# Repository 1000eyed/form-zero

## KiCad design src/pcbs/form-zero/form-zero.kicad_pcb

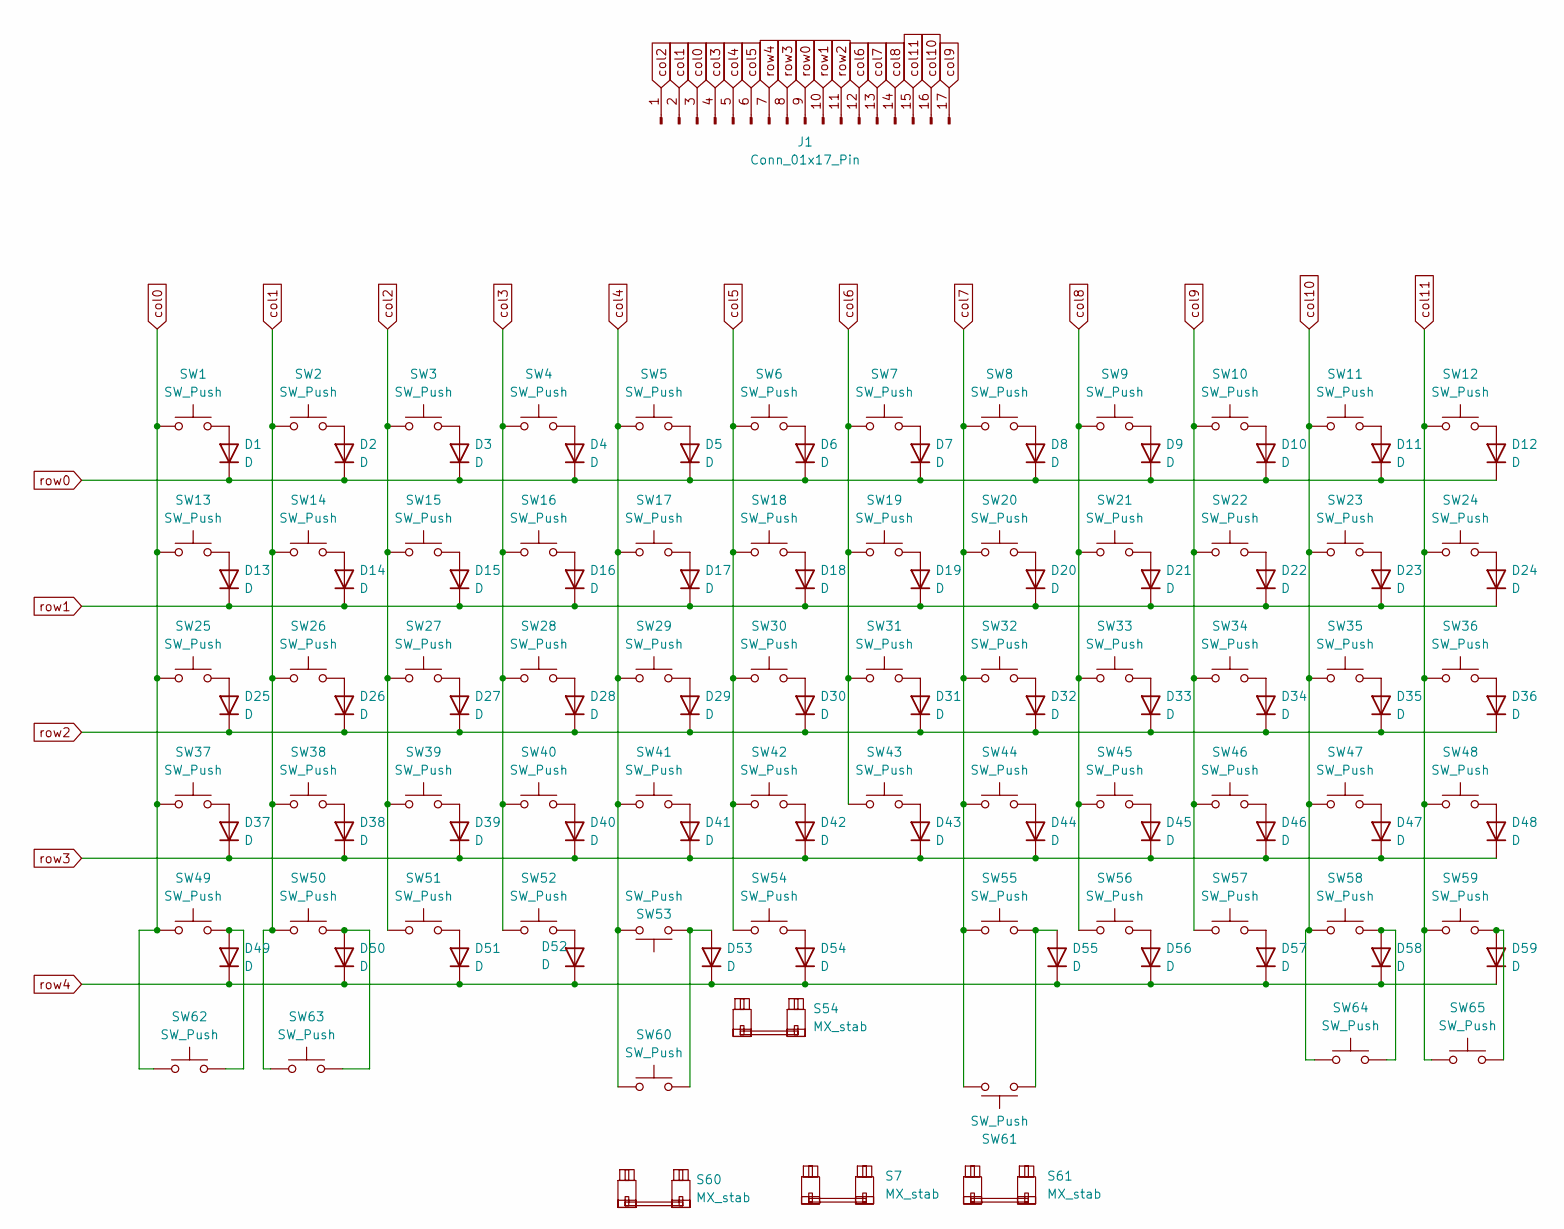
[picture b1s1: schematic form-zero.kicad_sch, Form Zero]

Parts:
D1, D2, D3, D4, D5, D6, D7, D8, D9, D10, D11, D12, D13, D14, D15, D16, D17, D18, D19, D20, D21, D22, D23, D24, D25, D26, D27, D28, D29, D30, D31, D32, D33, D34, D35, D36, D37, D38, D39, D40, D41, D42, D43, D44, D45, D46, D47, D48, D49, D50, D51, D52, D53, D54, D55, D56, D57, D58, D59: D; D3_TH_SMD_v2
J1: Conn_01x17_Pin; PinHeader_1x17_P2.54mm_Vertical
S7: MX_stab; STAB_MX_7u
S54, S60, S61: MX_stab; STAB_MX_2u
SW1, SW2, SW3, SW4, SW5, SW6, SW7, SW8, SW9, SW10, SW11, SW12, SW13, SW14, SW15, SW16, SW17, SW18, SW19, SW20, SW21, SW22, SW23, SW24, SW25, SW26, SW27, SW28, SW29, SW30, SW31, SW32, SW33, SW34, SW35, SW36, SW37, SW38, SW39, SW40, SW41, SW42, SW43, SW44, SW45, SW46, SW47, SW48, SW49, SW50, SW51, SW52, SW53, SW54, SW55, SW56, SW57, SW58, SW59, SW60, SW61: SW_Push; SW_MX_HS_CPG151101S11_1u
SW62, SW63, SW64, SW65: SW_Push; SW_MX_HS_CPG151101S11_1.25u

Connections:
unnamed: D1.2 (A), SW1.2
unnamed: D2.2 (A), SW2.2
unnamed: D3.2 (A), SW3.2
unnamed: D4.2 (A), SW4.2
unnamed: D5.2 (A), SW5.2
unnamed: D6.2 (A), SW6.2
unnamed: D7.2 (A), SW7.2
unnamed: D8.2 (A), SW8.2
unnamed: D9.2 (A), SW9.2
unnamed: D10.2 (A), SW10.2
unnamed: D11.2 (A), SW11.2
unnamed: D12.2 (A), SW12.2
unnamed: D13.2 (A), SW13.2
unnamed: D14.2 (A), SW14.2
unnamed: D15.2 (A), SW15.2
unnamed: D16.2 (A), SW16.2
unnamed: D17.2 (A), SW17.2
unnamed: D18.2 (A), SW18.2
unnamed: D19.2 (A), SW19.2
unnamed: D20.2 (A), SW20.2
unnamed: D21.2 (A), SW21.2
unnamed: D22.2 (A), SW22.2
unnamed: D23.2 (A), SW23.2
unnamed: D24.2 (A), SW24.2
unnamed: D25.2 (A), SW25.2
unnamed: D26.2 (A), SW26.2
unnamed: D27.2 (A), SW27.2
unnamed: D28.2 (A), SW28.2
unnamed: D29.2 (A), SW29.2
unnamed: D30.2 (A), SW30.2
unnamed: D31.2 (A), SW31.2
unnamed: D32.2 (A), SW32.2
unnamed: D33.2 (A), SW33.2
unnamed: D34.2 (A), SW34.2
unnamed: D35.2 (A), SW35.2
unnamed: D36.2 (A), SW36.2
unnamed: D37.2 (A), SW37.2
unnamed: D38.2 (A), SW38.2
unnamed: D39.2 (A), SW39.2
unnamed: D40.2 (A), SW40.2
unnamed: D41.2 (A), SW41.2
unnamed: D42.2 (A), SW42.2
unnamed: D43.2 (A), SW43.2
unnamed: D44.2 (A), SW44.2
unnamed: D45.2 (A), SW45.2
unnamed: D46.2 (A), SW46.2
unnamed: D47.2 (A), SW47.2
unnamed: D48.2 (A), SW48.2
unnamed: D49.2 (A), SW49.2, SW62.2
unnamed: D50.2 (A), SW50.2, SW63.2
unnamed: D51.2 (A), SW51.2
unnamed: D52.2 (A), SW52.2
unnamed: D53.2 (A), SW53.1, SW60.2
unnamed: D54.2 (A), SW54.2
unnamed: D55.2 (A), SW55.2, SW61.1
unnamed: D56.2 (A), SW56.2
unnamed: D57.2 (A), SW57.2
unnamed: D58.2 (A), SW58.2, SW64.2
unnamed: D59.2 (A), SW59.2, SW65.2
col0: J1.3, SW1.1, SW13.1, SW25.1, SW37.1, SW49.1, SW62.1
col1: J1.2, SW2.1, SW14.1, SW26.1, SW38.1, SW50.1, SW63.1
col2: J1.1, SW3.1, SW15.1, SW27.1, SW39.1, SW51.1
col3: J1.4, SW4.1, SW16.1, SW28.1, SW40.1, SW52.1
col4: J1.5, SW5.1, SW17.1, SW29.1, SW41.1, SW53.2, SW60.1
col5: J1.6, SW6.1, SW18.1, SW30.1, SW42.1, SW54.1
col6: J1.12, SW7.1, SW19.1, SW31.1, SW43.1
col7: J1.13, SW8.1, SW20.1, SW32.1, SW44.1, SW55.1, SW61.2
col8: J1.14, SW9.1, SW21.1, SW33.1, SW45.1, SW56.1
col9: J1.17, SW10.1, SW22.1, SW34.1, SW46.1, SW57.1
col10: J1.16, SW11.1, SW23.1, SW35.1, SW47.1, SW58.1, SW64.1
col11: J1.15, SW12.1, SW24.1, SW36.1, SW48.1, SW59.1, SW65.1
row0: D1.1 (K), D2.1 (K), D3.1 (K), D4.1 (K), D5.1 (K), D6.1 (K), D7.1 (K), D8.1 (K), D9.1 (K), D10.1 (K), D11.1 (K), D12.1 (K), J1.9
row1: D13.1 (K), D14.1 (K), D15.1 (K), D16.1 (K), D17.1 (K), D18.1 (K), D19.1 (K), D20.1 (K), D21.1 (K), D22.1 (K), D23.1 (K), D24.1 (K), J1.10
row2: D25.1 (K), D26.1 (K), D27.1 (K), D28.1 (K), D29.1 (K), D30.1 (K), D31.1 (K), D32.1 (K), D33.1 (K), D34.1 (K), D35.1 (K), D36.1 (K), J1.11
row3: D37.1 (K), D38.1 (K), D39.1 (K), D40.1 (K), D41.1 (K), D42.1 (K), D43.1 (K), D44.1 (K), D45.1 (K), D46.1 (K), D47.1 (K), D48.1 (K), J1.8
row4: D49.1 (K), D50.1 (K), D51.1 (K), D52.1 (K), D53.1 (K), D54.1 (K), D55.1 (K), D56.1 (K), D57.1 (K), D58.1 (K), D59.1 (K), J1.7

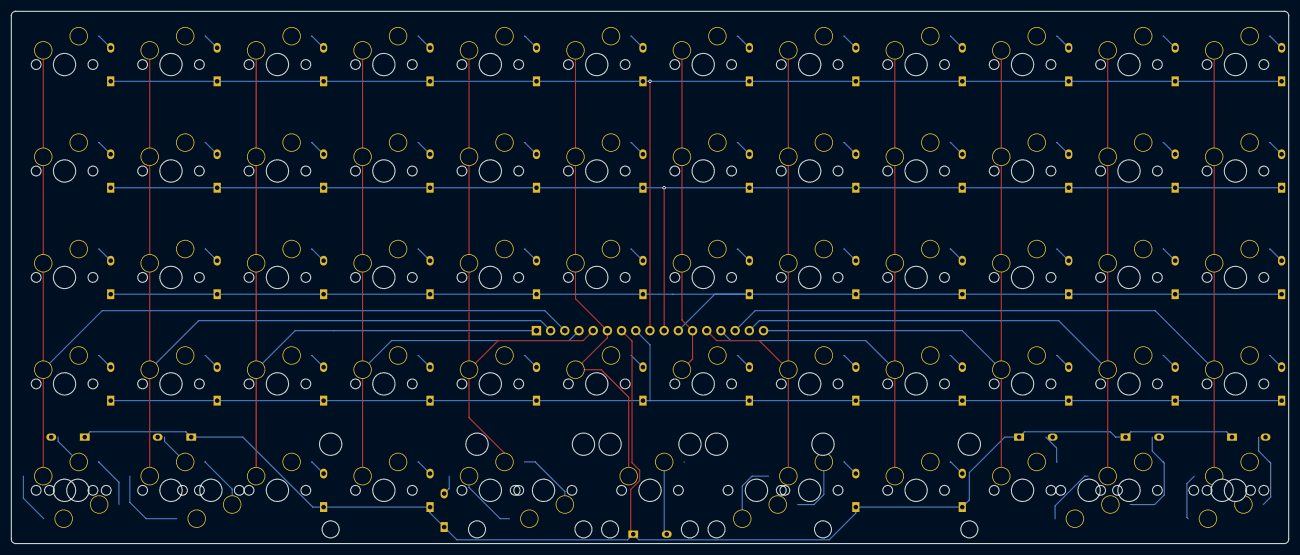
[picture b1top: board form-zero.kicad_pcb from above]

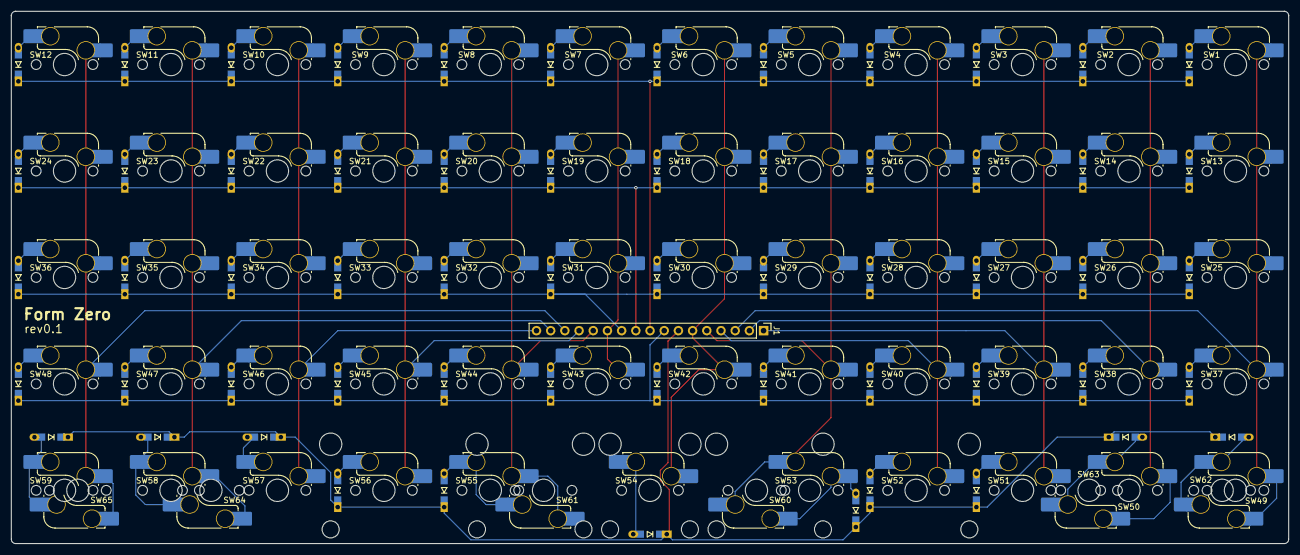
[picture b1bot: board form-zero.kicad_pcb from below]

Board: 2 copper layers, 228.6 x 95.2 mm, 129 parts (125 on the bottom side), 76 nets.

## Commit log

2024-08-11 add bottom row: 1.25, 1.25, 7, 1.25, 1.25
